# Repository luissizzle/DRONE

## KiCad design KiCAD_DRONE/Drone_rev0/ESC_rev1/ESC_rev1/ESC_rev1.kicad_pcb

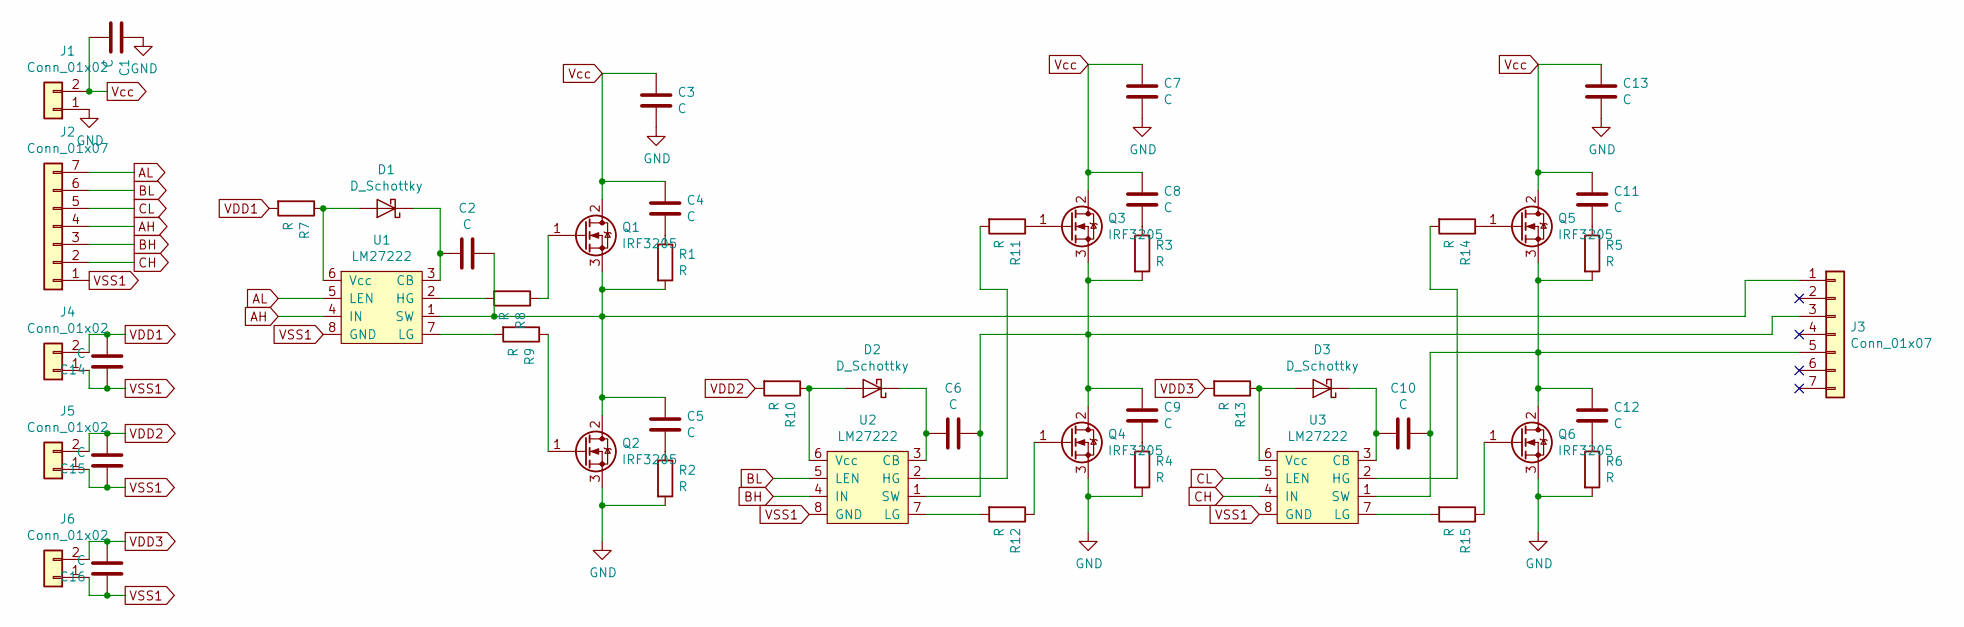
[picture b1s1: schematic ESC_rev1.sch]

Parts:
C1, C2, C3, C4, C5, C6, C7, C8, C9, C10, C11, C12, C13, C14, C15, C16: C; C_0805_2012Metric
D1, D2, D3: D_Schottky; D_A-405_P7.62mm_Horizontal
J1: Conn_01x02; PinHeader_1x02_P2.54mm_Vertical
J2: Conn_01x07; JST_EH_B07B-EH-A_1x07_P2.50mm_Vertical
J3: Conn_01x07; PinHeader_1x07_P2.54mm_Vertical
J4, J5, J6: Conn_01x02; JST_EH_B02B-EH-A_1x02_P2.50mm_Vertical
Q1, Q2, Q3, Q4, Q5, Q6: IRF3205; TO-220-3_Vertical
R1, R2, R3, R4, R5, R6, R7, R8, R9, R10, R11, R12, R13, R14, R15: R; R_0805_2012Metric
U1, U2, U3: LM27222; SOIC-8_3.9x4.9mm_P1.27mm

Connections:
AH: J2.4, U1.4 (IN)
AL: J2.7, U1.5 (LEN)
BH: J2.3, U2.4 (IN)
BL: J2.6, U2.5 (LEN)
CH: J2.2, U3.4 (IN)
CL: J2.5, U3.5 (LEN)
GND: C1.2, C3.1, C7.1, C13.1, J1.1, Q2.3 (S), Q4.3 (S), Q6.3 (S), R2.2, R4.2, R6.2
unnamed: C2.1, C5.2, J3.1, Q1.3 (S), Q2.2 (D), R1.2, U1.1 (SW)
unnamed: C2.2, D1.1 (K), U1.3 (CB)
unnamed: C4.1, R1.1
unnamed: C5.1, R2.1
unnamed: C6.1, C9.2, J3.3, Q3.3 (S), Q4.2 (D), R3.2, U2.1 (SW)
unnamed: C6.2, D2.1 (K), U2.3 (CB)
unnamed: C8.1, R3.1
unnamed: C9.1, R4.1
unnamed: C10.1, C12.2, J3.5, Q5.3 (S), Q6.2 (D), R5.2, U3.1 (SW)
unnamed: C10.2, D3.1 (K), U3.3 (CB)
unnamed: C11.1, R5.1
unnamed: C12.1, R6.1
unnamed: D1.2 (A), R7.1, U1.6 (Vcc)
unnamed: D2.2 (A), R10.1, U2.6 (Vcc)
unnamed: D3.2 (A), R13.1, U3.6 (Vcc)
unnamed: Q1.1 (G), R8.1
unnamed: Q2.1 (G), R9.1
unnamed: Q3.1 (G), R11.1
unnamed: Q4.1 (G), R12.1
unnamed: Q5.1 (G), R14.1
unnamed: Q6.1 (G), R15.1
unnamed: R8.2, U1.2 (HG)
unnamed: R9.2, U1.7 (LG)
unnamed: R11.2, U2.2 (HG)
unnamed: R12.2, U2.7 (LG)
unnamed: R14.2, U3.2 (HG)
unnamed: R15.2, U3.7 (LG)
VDD1: C14.1, J4.2, R7.2
VDD2: C15.1, J5.2, R10.2
VDD3: C16.1, J6.2, R13.2
VSS1: C14.2, C15.2, C16.2, J2.1, J4.1, J5.1, J6.1, U1.8 (GND), U2.8 (GND), U3.8 (GND)
Vcc: C1.1, C3.2, C4.2, C7.2, C8.2, C11.2, C13.2, J1.2, Q1.2 (D), Q3.2 (D), Q5.2 (D)

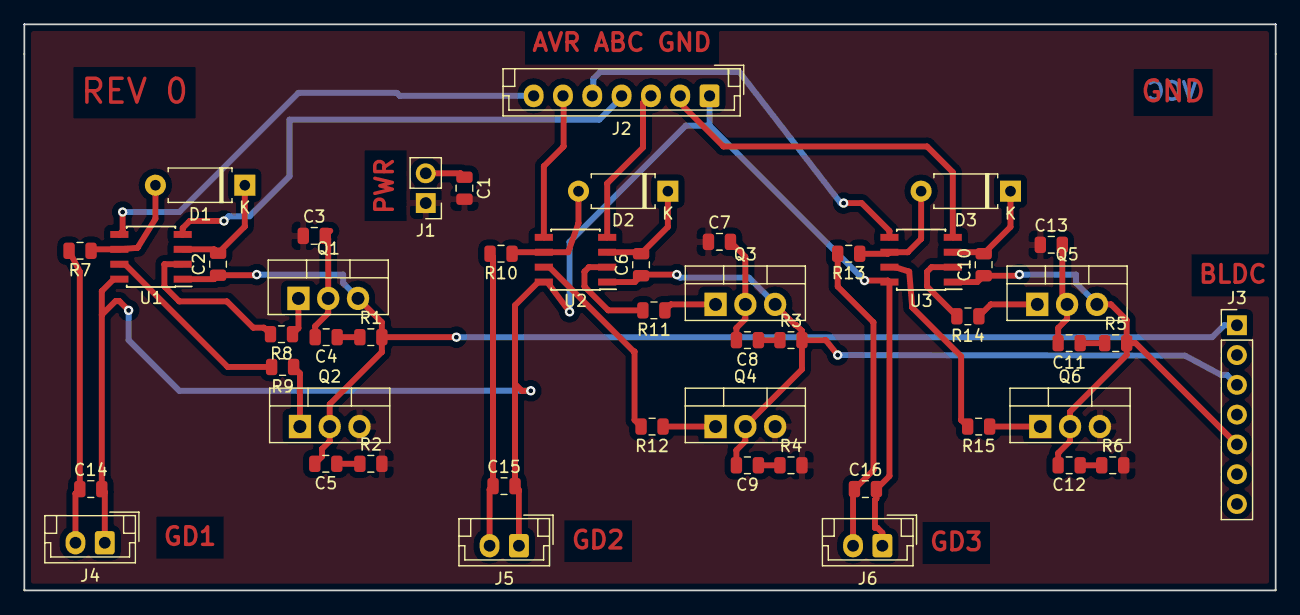
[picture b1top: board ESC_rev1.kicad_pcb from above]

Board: 2 copper layers, 106.7 x 48.3 mm, 49 parts (0 on the bottom side), 39 nets.

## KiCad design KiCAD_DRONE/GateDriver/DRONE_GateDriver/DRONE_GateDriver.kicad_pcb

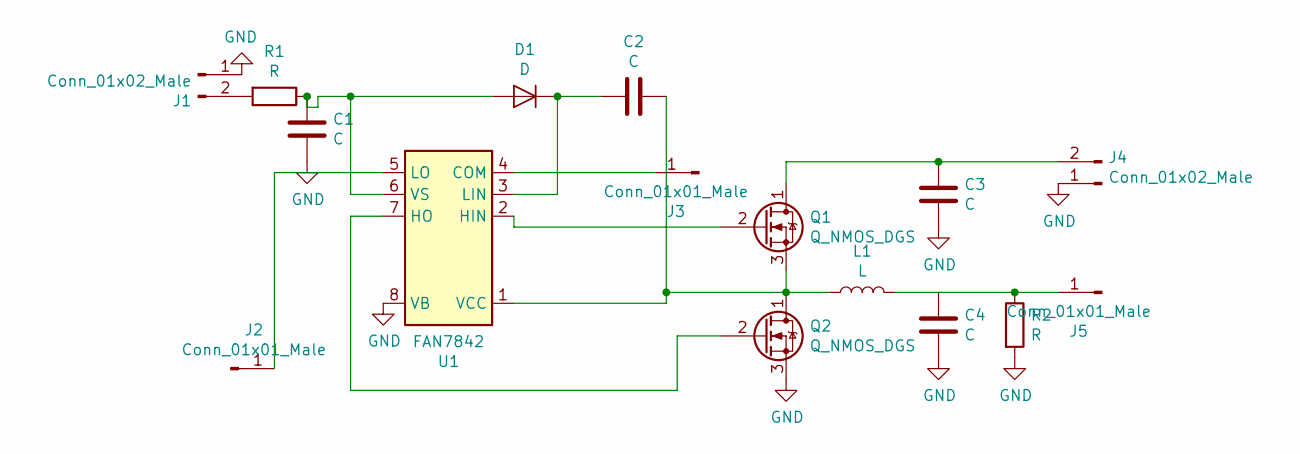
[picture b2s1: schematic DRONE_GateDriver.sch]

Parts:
C1, C2, C3, C4: C; C_0805_2012Metric
D1: D; D_DO-41_SOD81_P10.16mm_Horizontal
J1, J4: Conn_01x02_Male; header_2_pins
J2, J3, J5: Conn_01x01_Male; PinHeader_1x01_P1.00mm_Vertical
L1: L; L_0805_2012Metric
Q1, Q2: Q_NMOS_DGS; TO-92L_Inline_Wide
R1, R2: R; R_0805_2012Metric
U1: FAN7842; SOIC-8_3.9x4.9mm_P1.27mm

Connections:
GND: C1.2, C3.2, C4.2, J1.1, J4.1, Q2.3 (S), R2.2, U1.8 (VB)
unnamed: C1.1, D1.2 (A), R1.1, U1.6 (VS)
unnamed: C2.1, L1.1, Q1.3 (S), Q2.1 (D), U1.1 (VCC)
unnamed: C2.2, D1.1 (K), U1.3 (LIN)
unnamed: C3.1, J4.2, Q1.1 (D)
unnamed: C4.1, J5.1, L1.2, R2.1
unnamed: J1.2, R1.2
unnamed: J2.1, U1.5 (LO)
unnamed: J3.1, U1.4 (COM)
unnamed: Q1.2 (G), U1.2 (HIN)
unnamed: Q2.2 (G), U1.7 (HO)

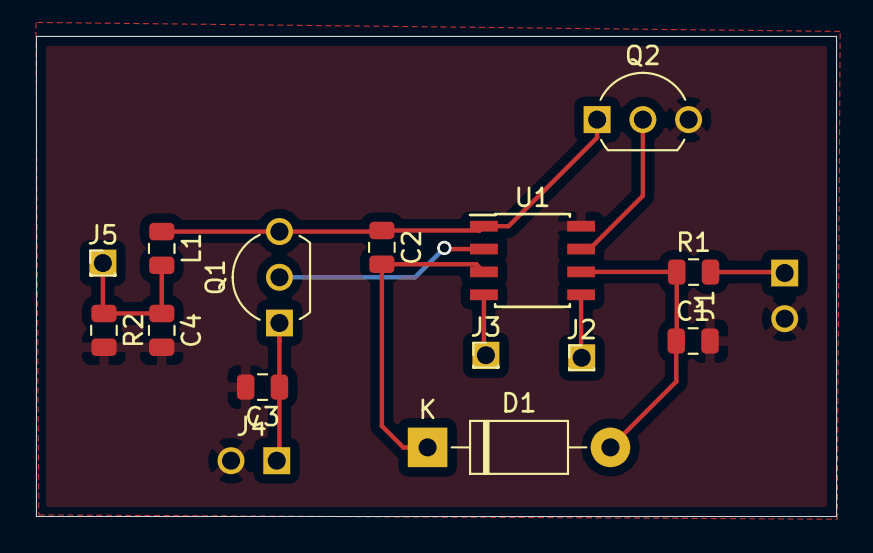
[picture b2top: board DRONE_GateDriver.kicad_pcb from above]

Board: 2 copper layers, 44.4 x 26.7 mm, 16 parts (0 on the bottom side), 11 nets.

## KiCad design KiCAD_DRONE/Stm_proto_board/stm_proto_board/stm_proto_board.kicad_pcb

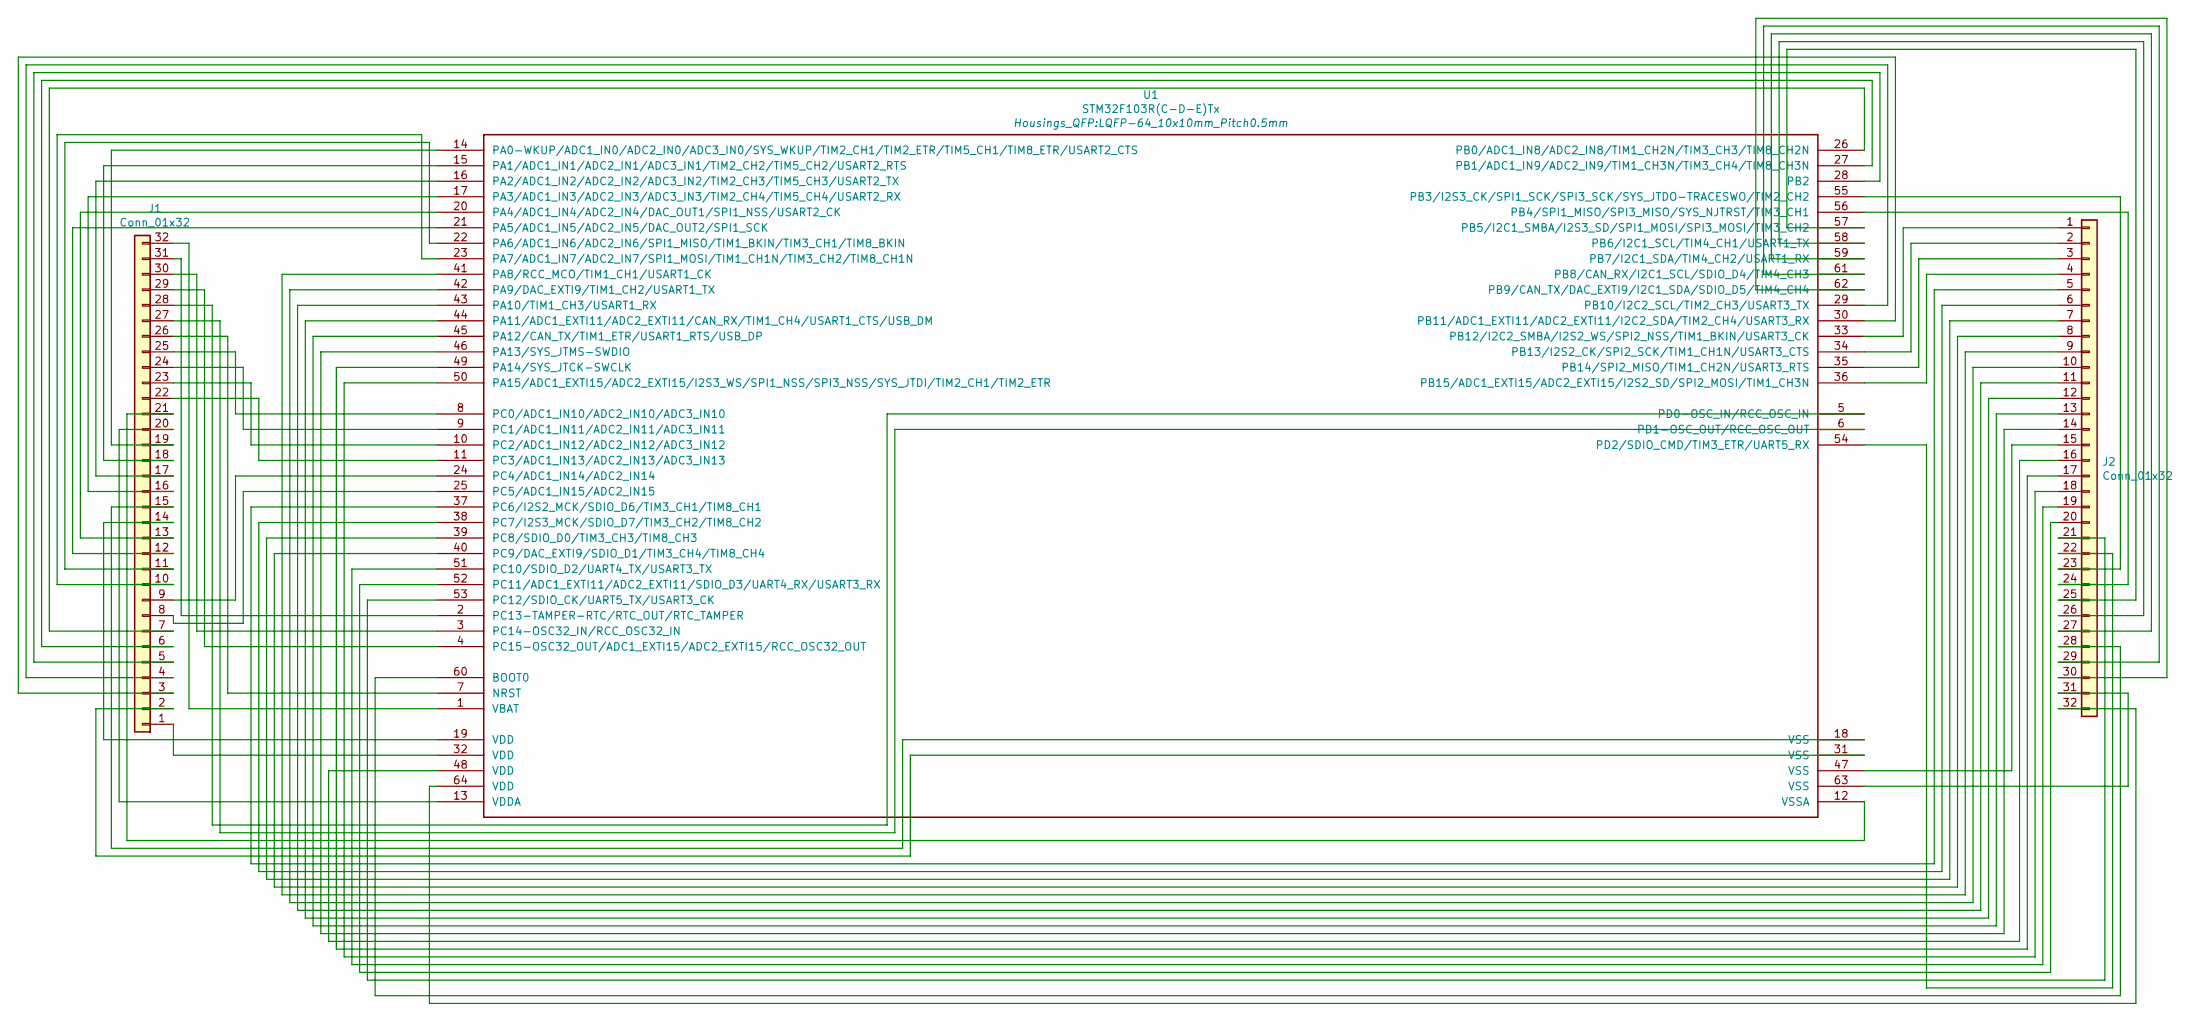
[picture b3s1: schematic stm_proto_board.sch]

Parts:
J1, J2: Conn_01x32; PinHeader_1x32_P2.54mm_Vertical
U1: STM32F103R(C-D-E)Tx; LQFP-64_10x10mm_Pitch0.5mm

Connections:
unnamed: J1.1, U1.32 (VDD)
unnamed: J1.2, U1.31 (VSS)
unnamed: J1.3, U1.30 (PB11/ADC1_EXTI11/ADC2_EXTI11/I2C2_SDA/T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)
unnamed: J1.4, U1.29 (PB10/I2C2_SCL/TIM2_CH3/USART3_TX)
unnamed: J1.5, U1.28 (PB2)
unnamed: J1.6, U1.27 (PB1/ADC1_IN9/ADC2_IN9/TIM1_CH3N/TIM3_CH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)
unnamed: J1.7, U1.26 (PB0/ADC1_IN8/ADC2_IN8/TIM1_CH2N/TIM3_CH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)
unnamed: J1.8, U1.25 (PC5/ADC1_IN15/ADC2_IN15)
unnamed: J1.9, U1.24 (PC4/ADC1_IN14/ADC2_IN14)
unnamed: J1.10, U1.23 (PA7/ADC1_IN7/ADC2_IN7/SPI1_MOSI/TIM1_CH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)
unnamed: J1.11, U1.22 (PA6/ADC1_IN6/ADC2_IN6/SPI1_MISO/TIM1_BK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)
unnamed: J1.12, U1.21 (PA5/ADC1_IN5/ADC2_IN5/DAC_OUT2/SPI1_SCK)
unnamed: J1.13, U1.20 (PA4/ADC1_IN4/ADC2_IN4/DAC_OUT1/SPI1_NSS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)
unnamed: J1.14, U1.19 (VDD)
unnamed: J1.15, U1.18 (VSS)
unnamed: J1.16, U1.17 (PA3/ADC1_IN3/ADC2_IN3/ADC3_IN3/TIM2_CH4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)
unnamed: J1.17, U1.16 (PA2/ADC1_IN2/ADC2_IN2/ADC3_IN2/TIM2_CH3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)
unnamed: J1.18, U1.15 (PA1/ADC1_IN1/ADC2_IN1/ADC3_IN1/TIM2_CH2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)
unnamed: J1.19, U1.14 (PA0-WKUP/ADC1_IN0/ADC2_IN0/ADC3_IN0/SYS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)
unnamed: J1.20, U1.13 (VDDA)
unnamed: J1.21, U1.12 (VSSA)
unnamed: J1.22, U1.11 (PC3/ADC1_IN13/ADC2_IN13/ADC3_IN13)
unnamed: J1.23, U1.10 (PC2/ADC1_IN12/ADC2_IN12/ADC3_IN12)
unnamed: J1.24, U1.9 (PC1/ADC1_IN11/ADC2_IN11/ADC3_IN11)
unnamed: J1.25, U1.8 (PC0/ADC1_IN10/ADC2_IN10/ADC3_IN10)
unnamed: J1.26, U1.7 (NRST)
unnamed: J1.27, U1.6 (PD1-OSC_OUT/RCC_OSC_OUT)
unnamed: J1.28, U1.5 (PD0-OSC_IN/RCC_OSC_IN)
unnamed: J1.29, U1.4 (PC15-OSC32_OUT/ADC1_EXTI15/ADC2_EXTI15/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)
unnamed: J1.30, U1.3 (PC14-OSC32_IN/RCC_OSC32_IN)
unnamed: J1.31, U1.2 (PC13-TAMPER-RTC/RTC_OUT/RTC_TAMPER)
unnamed: J1.32, U1.1 (VBAT)
unnamed: J2.1, U1.33 (PB12/I2C2_SMBA/I2S2_WS/SPI2_NSS/TIM1_BK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)
unnamed: J2.2, U1.34 (PB13/I2S2_CK/SPI2_SCK/TIM1_CH1N/USART3_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)
unnamed: J2.3, U1.35 (PB14/SPI2_MISO/TIM1_CH2N/USART3_RTS)
unnamed: J2.4, U1.36 (PB15/ADC1_EXTI15/ADC2_EXTI15/I2S2_SD/SP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)
unnamed: J2.5, U1.37 (PC6/I2S2_MCK/SDIO_D6/TIM3_CH1/TIM8_CH1)
unnamed: J2.6, U1.38 (PC7/I2S3_MCK/SDIO_D7/TIM3_CH2/TIM8_CH2)
unnamed: J2.7, U1.39 (PC8/SDIO_D0/TIM3_CH3/TIM8_CH3)
unnamed: J2.8, U1.40 (PC9/DAC_EXTI9/SDIO_D1/TIM3_CH4/TIM8_CH4)
unnamed: J2.9, U1.41 (PA8/RCC_MCO/TIM1_CH1/USART1_CK)
unnamed: J2.10, U1.42 (PA9/DAC_EXTI9/TIM1_CH2/USART1_TX)
unnamed: J2.11, U1.43 (PA10/TIM1_CH3/USART1_RX)
unnamed: J2.12, U1.44 (PA11/ADC1_EXTI11/ADC2_EXTI11/CAN_RX/TIM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)
unnamed: J2.13, U1.45 (PA12/CAN_TX/TIM1_ETR/USART1_RTS/USB_DP)
unnamed: J2.14, U1.46 (PA13/SYS_JTMS-SWDIO)
unnamed: J2.15, U1.47 (VSS)
unnamed: J2.16, U1.48 (VDD)
unnamed: J2.17, U1.49 (PA14/SYS_JTCK-SWCLK)
unnamed: J2.18, U1.50 (PA15/ADC1_EXTI15/ADC2_EXTI15/I2S3_WS/SP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)
unnamed: J2.19, U1.51 (PC10/SDIO_D2/UART4_TX/USART3_TX)
unnamed: J2.20, U1.52 (PC11/ADC1_EXTI11/ADC2_EXTI11/SDIO_D3/UA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)
unnamed: J2.21, U1.53 (PC12/SDIO_CK/UART5_TX/USART3_CK)
unnamed: J2.22, U1.54 (PD2/SDIO_CMD/TIM3_ETR/UART5_RX)
unnamed: J2.23, U1.55 (PB3/I2S3_CK/SPI1_SCK/SPI3_SCK/SYS_JTDO-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)
unnamed: J2.24, U1.56 (PB4/SPI1_MISO/SPI3_MISO/SYS_NJTRST/TIM3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)
unnamed: J2.25, U1.57 (PB5/I2C1_SMBA/I2S3_SD/SPI1_MOSI/SPI3_MO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)
unnamed: J2.26, U1.58 (PB6/I2C1_SCL/TIM4_CH1/USART1_TX)
unnamed: J2.27, U1.59 (PB7/I2C1_SDA/TIM4_CH2/USART1_RX)
unnamed: J2.28, U1.60 (BOOT0)
unnamed: J2.29, U1.61 (PB8/CAN_RX/I2C1_SCL/SDIO_D4/TIM4_CH3)
unnamed: J2.30, U1.62 (PB9/CAN_TX/DAC_EXTI9/I2C1_SDA/SDIO_D5/T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)
unnamed: J2.31, U1.63 (VSS)
unnamed: J2.32, U1.64 (VDD)

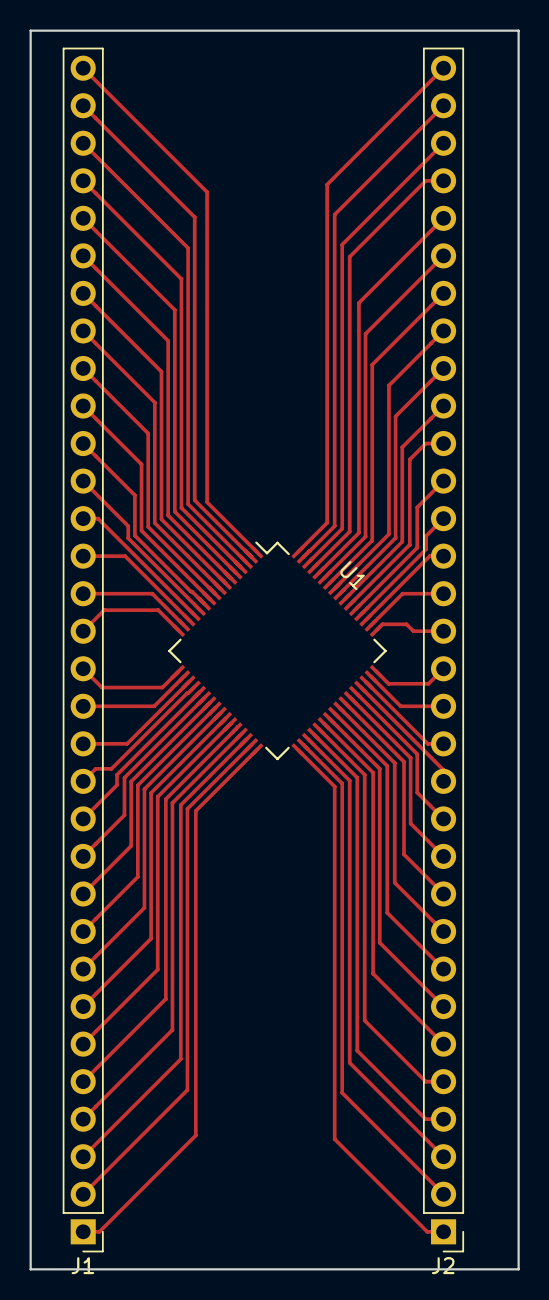
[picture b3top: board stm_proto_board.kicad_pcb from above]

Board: 2 copper layers, 33.0 x 83.8 mm, 3 parts (0 on the bottom side), 64 nets.

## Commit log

2019-01-03 added old files including CAD and datasheets
2019-01-03 added code 'test1'
2019-01-14 18650 datasheet
2019-01-14 rough drone schematic
2019-01-16 added drawn schem
2019-04-07 Added recent FET purchases datasheets, cleaned up folders
2019-05-07 added new kicad file and updated code
2019-05-08 updated code, made unused phase open
2019-05-08 added negative phases! to code
2019-05-08 changed delay time to 0.01 for 6-step code
2019-05-17 finalized workng PWM with port manipulation i /PWM_PortX_test, cant used atmega328P, this code is obselete and will be archived. Added app note on gate drivers
2019-05-17 Deleted code replicates. cleaned folders
2019-05-17 added order sheet
2019-05-22 added two applicaton notes for stm32 and the datasheet. kicad project for stm protoboard
2019-05-23 added the m60 files for the stm proto board and the gate driver IC. updated code to drive motor. not sure if it works or not.
2019-05-25 added gate driver kicad files
2019-05-26 added ESC rev1, with gate drivers
2019-05-26 add gate driver and comparater datasheets, gate driver app note, and stm app note
2019-06-01 finished ESC rev1 layout!
2019-06-13 finshed ESC rev0 layout
2019-06-17 added text and final layout changes. added m60 files.
2019-07-13 added documents
2019-08-07 renamed folders to appropriate revisions. created rev0.1 kicad project. this will contain common grounds bewteen gate driver and FETs.
2019-08-07 added some CAD files local to BELs computer
